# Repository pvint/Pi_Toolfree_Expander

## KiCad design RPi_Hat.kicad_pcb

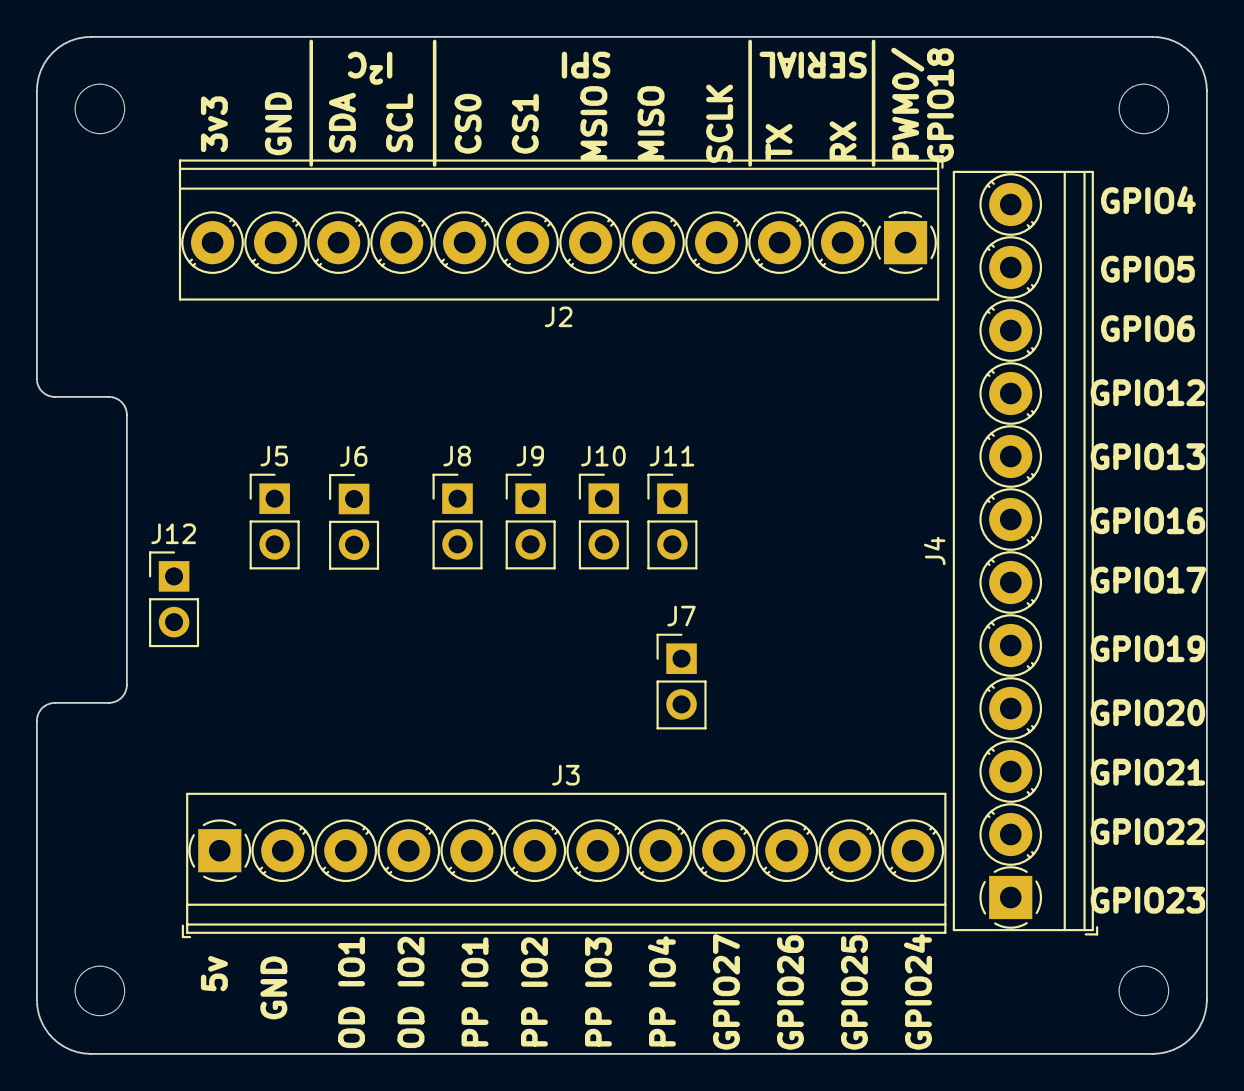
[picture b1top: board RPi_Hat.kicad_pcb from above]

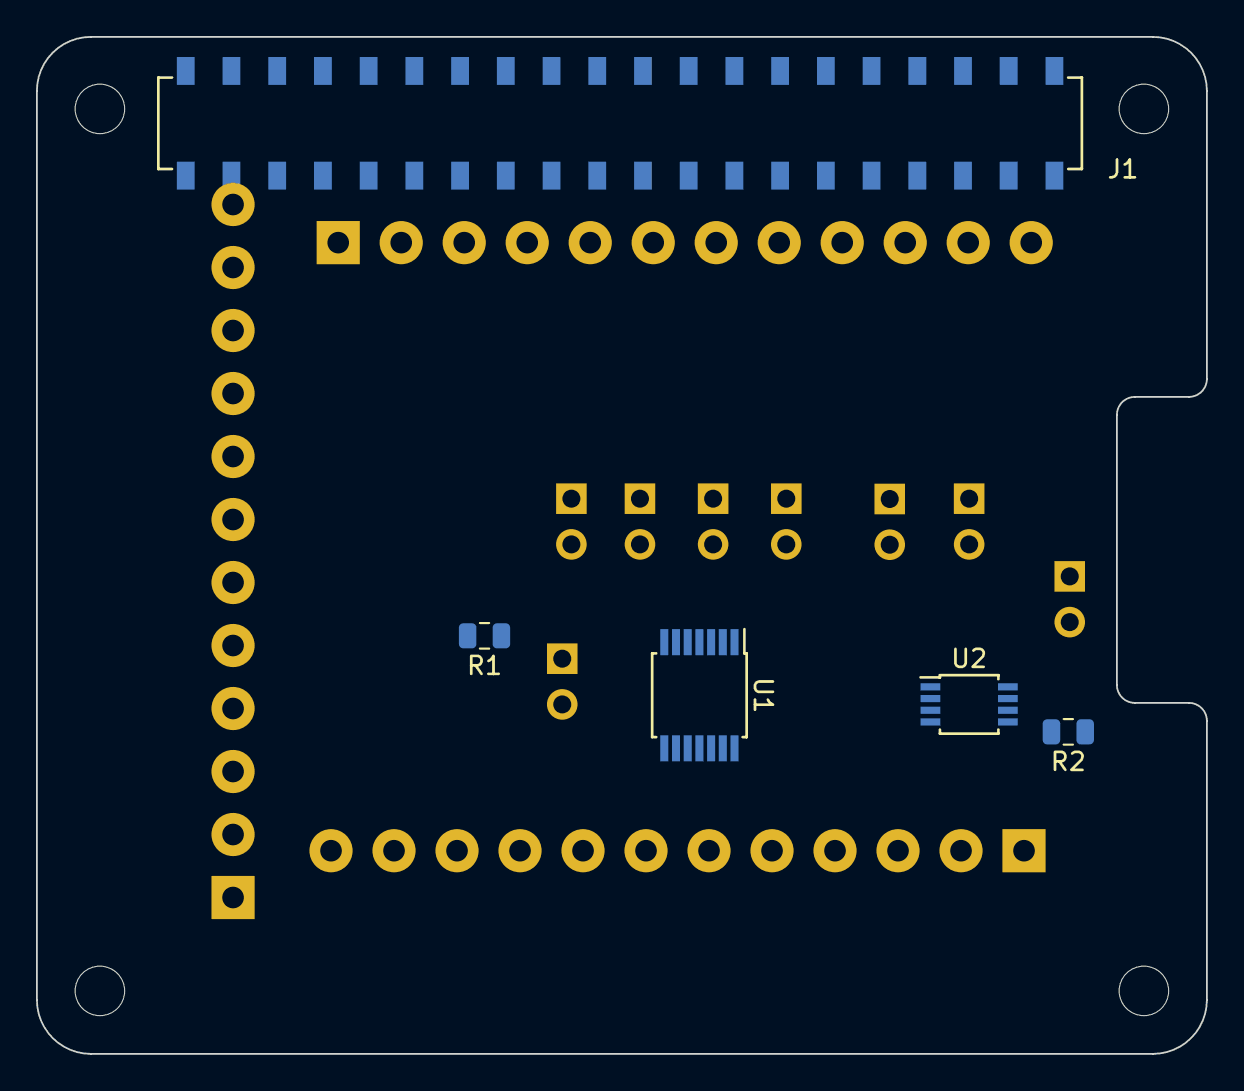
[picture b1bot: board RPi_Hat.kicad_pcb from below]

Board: 2 copper layers, 65.0 x 56.5 mm, 16 parts (5 on the bottom side), 43 nets, no tracks yet.

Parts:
J1: RPi_GPIO; Sullins_NPTC202KFMS-RC_PinSocket_2x20_P2.54mm_Vertical_SMD
J2, J3, J4: Conn_01x12_Female; TerminalBlock_Phoenix_PT-1,5-12-3.5-H_1x12_P3.50mm_Horizont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
J5, J6, J7, J8, J9, J10, J11, J12: Conn_01x02_Male; PinHeader_1x02_P2.54mm_Vertical
R1, R2: R; R_0805_2012Metric
U1: TXB0104PW; TSSOP-14_4.4x5mm_P0.65mm
U2: TXB0102DCT; TSSOP-8_3x3mm_P0.65mm

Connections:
3v3: J1.1, J1.17, J2.12, J7.2, J12.2, U1.1, U2.3
5v: J1.2, J1.4, J3.1, U1.14, U2.7
GND: J1.6, J1.9, J1.14, J1.20, J1.25, J1.30, J1.34, J1.39, J2.11, J3.2, R1.2, R2.2, U1.7, U2.2
GPIO2-SDA: J1.3, J2.10, J5.2
GPIO3-SCL: J1.5, J2.9, J6.2
GPIO4: J1.7, J4.12
GPIO5: J1.29, J4.11
GPIO6: J1.31, J4.10
GPIO7-CS1: J1.26, J2.7
GPIO8-CS0: J1.24, J2.8
GPIO9-MSIO: J1.21, J2.5
GPIO10-MOSI: J1.19, J2.6
GPIO11-SCK: J1.23, J2.4
GPIO12: J1.32, J4.9
GPIO13: J1.33, J4.8
GPIO14-TXD: J1.8, J2.3
GPIO15-RXD: J1.10, J2.2
GPIO16: J1.36, J4.7
GPIO17: J1.11, J4.6
GPIO18: J1.12, J2.1
GPIO19: J1.35, J4.5
GPIO20: J1.38, J4.4
GPIO21: J1.40, J4.3
GPIO22: J1.15, J4.2
GPIO23: J1.16, J4.1, J8.2
GPIO24: J1.18, J3.12, J9.2
GPIO25: J1.22, J3.11, J10.2
GPIO26: J1.37, J3.10, J11.2
GPIO27: J1.13, J3.9
unnamed: J5.1, U2.5
unnamed: J6.1, U2.4
unnamed: J7.1, R1.1, U1.8
unnamed: J8.1, U1.2
unnamed: J9.1, U1.3
unnamed: J10.1, U1.4
unnamed: J11.1, U1.5
unnamed: J12.1, R2.1, U2.6
OD_IO1: J3.3, U2.8
OD_IO2: J3.4, U2.1
PP_IO1: J3.5, U1.13
PP_IO2: J3.6, U1.12
PP_IO3: J3.7, U1.11
PP_IO4: J3.8, U1.10

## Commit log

2018-11-09 Initial import
2018-11-09 Added PDF of schematic and board images
